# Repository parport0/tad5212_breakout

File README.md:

# tad5212_breakout

A breakout board for TI's [TAD5212](https://www.ti.com/product/TAD5212) and [TAD5112](https://www.ti.com/product/TAD5112) DACs (they are drop-in replacements of each other).

Should work as both 2-layer and 4-layer boards. All signals are on layer 1.

If ordering the board with assembly, make sure the orientation of the tantalum caps is correct.

No guarantees on the level of noise, I am inexperienced in PCB design. Raise an issue if you have advice or ideas.

⚠️ I couldn't yet test if headset detection is working or not. The voltage levels on MICDET seem to change (when music is playing and jack detection is turned on via registers), but I could not confirm that the "is headset plugged in?" register value changes — need a kernel driver that allows reading from I2C when it's loaded.

|  |  |
| ------------------- | --------------------- |

## Usage

I test this board with [PocketBeagle 2](https://docs.beagle.cc/boards/pocketbeagle-2/), kernel 6.18.10, driver snd-soc-pcm6240, and **[this dtso](tad5x12.dtso)**.

Hookup:

| PocketBeagle 2 | Breakout |
| -------------- | -------- |
| P1.26          | SDA      |
| P1.28          | SCL      |
| P2.01          | BCLK     |
| P1.02          | DIN      |
| P1.04          | FSYNC    |
| P1.14          | +3V3     |
| P1.22          | GND      |

My configuration registers ([see binary](tad5212-i2c-2-1dev.bin)):

```
02 01  // DEV_MISC_CFG -- not in sleep
19 40  // 2 data outputs for Primary ASI, no data outputs for Secondary ASI
1a 70  // I2S mode, 32 bits, BCLK and FSYNC polarity standard
64 24  // Stereo single-ended (DAC1A / IN1M -> OUT1P ; DAC1B / IN1P -> OUT1M)
65 60  // OUT1P: headphone driver, 0dB
66 60  // OUT1M: headphone driver, 0dB
67 c9  // Channel 1A: Digital Volume Control set to 0 dB
69 c9  // Channel 1B: Digital Volume Control set to 0 dB
29 30  // TDM is slot 16 or I2S, LJ is right slot 0
76 0c  // CH_EN
78 40  // PWR_CFG
```

## Firmware editing

I do not use the TI tools for firmware editing (TI rejected my requests, likely because I categoried myself as a "hobbyist"), instead I change the firmware by hand.

The firmware is basically a bunch of headers surrounding a set of I2C register addresses and values to write. See [pcm6240.c](https://lwn.net/Articles/961340/).

If using ImHex, this pattern could be convenient to use:

```
#pragma endian big
import std.io;

enum blk_type: u8 {
    PCMDEVICE_BIN_BLK_COEFF = 1,
    PCMDEVICE_BIN_BLK_POST_POWER_UP = 2,
    PCMDEVICE_BIN_BLK_PRE_SHUTDOWN = 3,
    PCMDEVICE_BIN_BLK_PRE_POWER_UP = 4,
    PCMDEVICE_BIN_BLK_POST_SHUTDOWN = 5
};

enum subblk_type: u16 {
    PCMDEVICE_CMD_SING_W = 0x1,
    PCMDEVICE_CMD_BURST = 0x2,
    PCMDEVICE_CMD_DELAY = 0x3,
    PCMDEVICE_CMD_FIELD_W = 0x4,
};

fn format_hex(auto value) {
    return std::format("0x{:02X}", value);
};

struct reg_write_cmd {
    u16 dev_no [[color("888888")]];
    u8 reg [[format("format_hex"), color("FF0000")]];
    u8 value [[format("format_hex"), color("00FF00")]];
};

struct subblk {
    subblk_type subblk_type;
    u16 subblk_len;
    reg_write_cmd cmds[subblk_len];
};

struct data_block {
    u8 dev_idx;
    blk_type block_type;
    u16 yram_checksum;
    u32 block_size;
    u32 n_subblks;
    subblk subblk[n_subblks];
};

u32 file_size @ 0x00;
u32 checksum @ 0x04;
u32 binary_version @ 0x08;
u32 drv_fw_version @ 0x0C;
u8 plat_type @ 0x14;
u8 dev_family @ 0x15;
u8 reserve @ 0x16;

u8 ndev @ 0x17;
u8 devs[0x08] @ 0x18;
u32 nconfig @ 0x20;
u32 config_size[0x40] @ 0x24;

char config_name[0x40] @ 0x124;
u32 nblocks @ 0x164;

data_block data_block[nblocks] @ 0x168;
```

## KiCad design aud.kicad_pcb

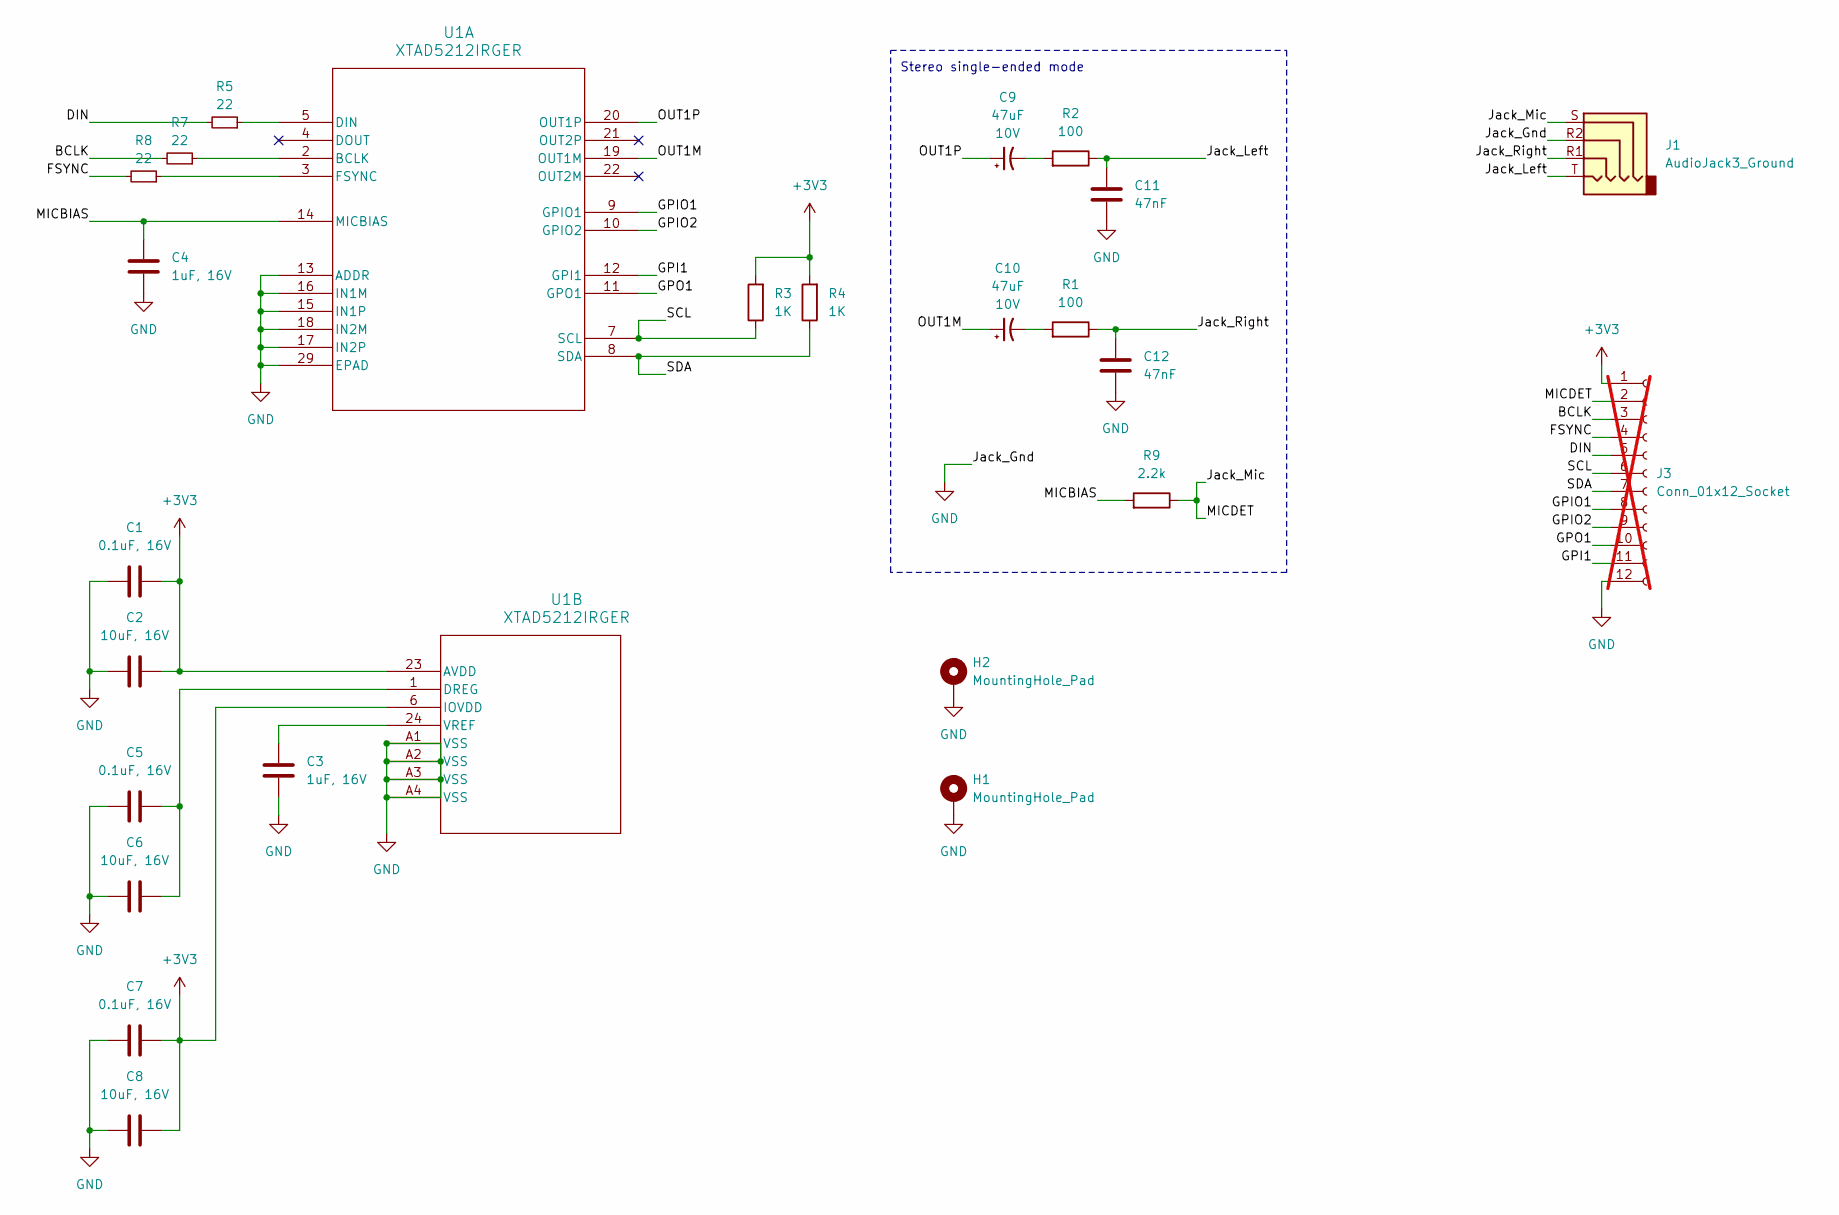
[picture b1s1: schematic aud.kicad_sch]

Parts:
C1, C5, C7: 0.1uF, 16V; C_0402_1005Metric; LCSC C14663
C2, C6, C8: 10uF, 16V; C_0805_2012Metric; LCSC C96446
C3, C4: 1uF, 16V; C_0603_1608Metric; LCSC C15849
C9, C10: 47uF; CP_EIA-3528-21_Kemet-B; Voltage 10V; LCSC C22036
C11, C12: 47nF; C_0603_1608Metric; LCSC C14663
H1, H2: MountingHole_Pad; MountingHole_2.2mm_M2_Pad
J1: AudioJack3_Ground; Jack_3.5mm_KoreanHropartsElec_PJ-320D-4A_Horizontal; LCSC C95562
J3: Conn_01x12_Socket; PinHeader_1x12_P2.54mm_Vertical; not fitted
R1, R2: 100; R_0603_1608Metric
R3, R4: 1K; R_0603_1608Metric
R5, R7, R8: 22; R_0603_1608Metric
R9: 2.2k; R_0603_1608Metric
U1: XTAD5212IRGER; VQFN24_RGE_CORNERPADS_TEX; LCSC C45068920

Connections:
+3V3: C1.2, C2.2, C7.2, C8.2, J3.1, R3.2, R4.2, U1.6 (IOVDD), U1.23 (AVDD)
/BCLK: J3.3, R7.2
/DIN: J3.5, R5.2
/FSYNC: J3.4, R8.2
/GPI1: J3.11, U1.12 (GPI1)
/GPIO1: J3.8, U1.9 (GPIO1)
/GPIO2: J3.9, U1.10 (GPIO2)
/GPO1: J3.10, U1.11 (GPO1)
/Jack_Left: C11.2, J1.T, R2.1
/Jack_Mic: J1.S, J3.2, R9.1
/Jack_Right: C12.2, J1.R1, R1.1
/MICBIAS: C4.2, R9.2, U1.14 (MICBIAS)
/OUT1M: C10.1, U1.19 (OUT1M)
/OUT1P: C9.1, U1.20 (OUT1P)
/SCL: J3.6, R3.1, U1.7 (SCL)
/SDA: J3.7, R4.1, U1.8 (SDA)
GND: C1.1, C2.1, C3.2, C4.1, C5.1, C6.1, C7.1, C8.1, C11.1, C12.1, H1.1, H2.1, J1.R2, J3.12, U1.13 (ADDR), U1.15 (IN1P), U1.16 (IN1M), U1.17 (IN2P), U1.18 (IN2M), U1.29 (EPAD), U1.A1 (VSS), U1.A2 (VSS), U1.A3 (VSS), U1.A4 (VSS)
unnamed: C9.2, R2.2
unnamed: C10.2, R1.2
unnamed: R7.1, U1.2 (BCLK)
unnamed: R5.1, U1.5 (DIN)
unnamed: R8.1, U1.3 (FSYNC)
unnamed: C5.2, C6.2, U1.1 (DREG)
unnamed: C3.1, U1.24 (VREF)

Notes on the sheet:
Stereo single-ended mode

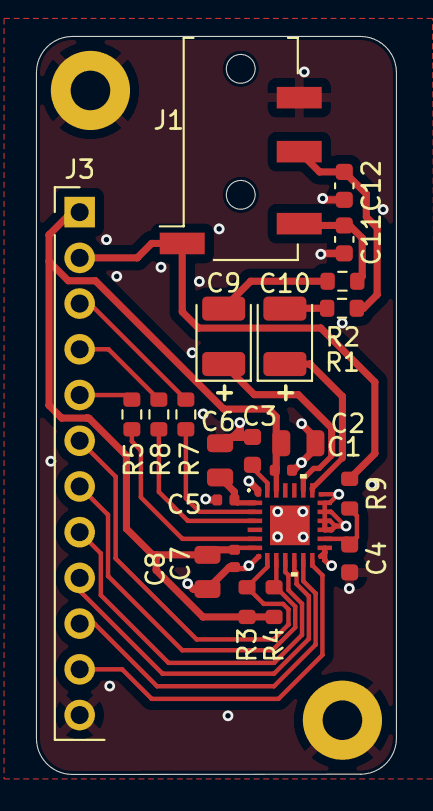
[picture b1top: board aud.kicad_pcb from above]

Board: 4 copper layers, 20.0 x 41.0 mm, 25 parts (0 on the bottom side), 24 nets.

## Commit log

2026-01-11 Initial, version 1 import
2026-02-13 Update to version 2
    * Fixes the main mistake of not adding AC coupling caps.
    * Adds a possibly working MICDET pin.
    * Does not break out DOUT anymore.
2026-03-08 Add Linux usage
2026-03-09 README.md: complain about TI
